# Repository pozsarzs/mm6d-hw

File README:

*** WARNING! It is not yet useable, because it is under development. WARNING ***

Short information
-----------------
MM6D * Remote controlled switching device
Copyright (C) 2020 Pozsár Zsolt <pozsar.zsolt@szerafingomba.hu>
Homepage: <http://www.szerafingomba.hu/equipments/>

Documentation
 - version:             1.0
 - licence:             CC-BY-NC-4.0
 - language:            en

Hardware
 - version:             v200612
 - architecture:        xtensa
 - operation system:    -

Software
 - version:             v0.1
 - licence:             EUPL v1.1
 - language:            en

*** WARNING! It is not yet useable, because it is under development. WARNING ***

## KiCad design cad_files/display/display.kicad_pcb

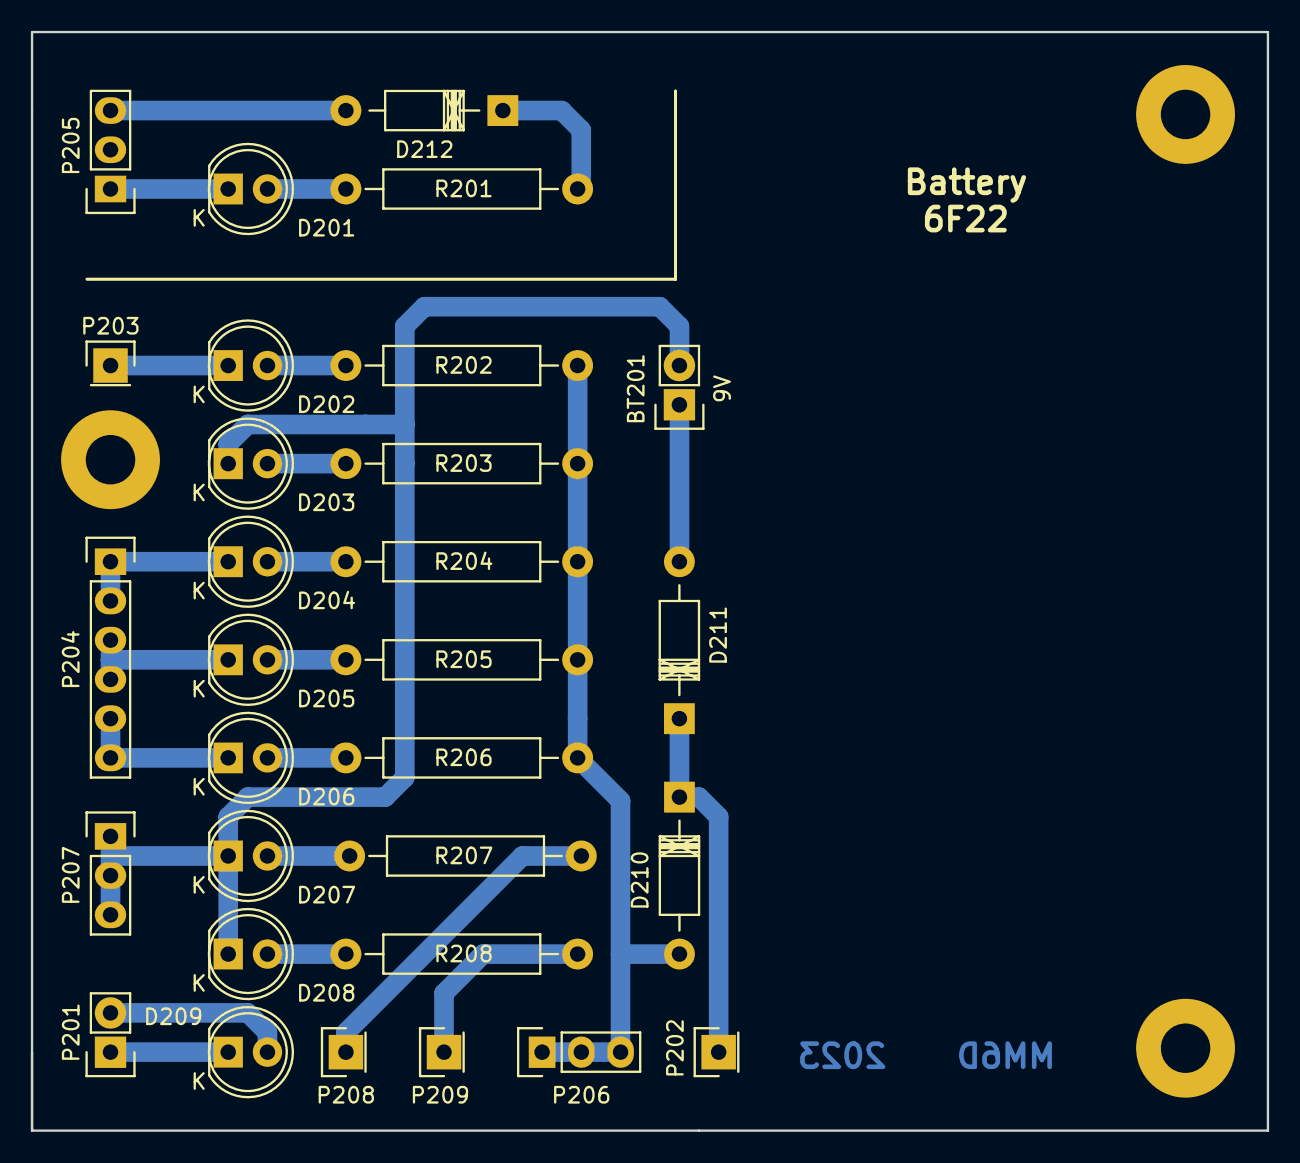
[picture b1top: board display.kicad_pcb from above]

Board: 2 copper layers, 80.0 x 71.1 mm, 30 parts (0 on the bottom side), 23 nets.

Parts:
BT201: 9V; Socket_Strip_Straight_1x02
D201, D203: white; LED-5MM
D202, D207: red; LED-5MM
D204, D205, D206: green; LED-5MM
D208: yellow; LED-5MM
D209: blue; LED-5MM
D210, D211: 1N4001; Diode_DO-41_SOD81_Horizontal_RM10
D212: 1N4007; Diode_DO-41_SOD81_Horizontal_RM10
P201: CONN_01X02; Socket_Strip_Straight_1x02
P202, P203, P208, P209: CONN_01X01; Socket_Strip_Straight_1x01
P204: CONN_01X06; Socket_Strip_Straight_1x06
P205, P206, P207: CONN_01X03; Socket_Strip_Straight_1x03
R201: 47k; Resistor_Horizontal_RM15mm
R202, R203: 1.5k; Resistor_Horizontal_RM15mm
R204, R205, R206, R207, R208: 1,5k; Resistor_Horizontal_RM15mm

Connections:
/+12V: D210.2, P206.1, P206.2, P206.3, R202.2, R203.2, R204.2, R205.2, R206.2
unnamed: BT201.1, D211.2
unnamed: BT201.2, D203.1, D207.1, D208.1, P207.1, P207.2, P207.3
unnamed: D201.1, P205.1
unnamed: D201.2, R201.1
unnamed: D202.1, P203.1
unnamed: D202.2, R202.1
unnamed: D203.2, R203.1
unnamed: D204.1, P204.1, P204.2
unnamed: D204.2, R204.1
unnamed: D205.1, P204.3, P204.4
unnamed: D205.2, R205.1
unnamed: D206.1, P204.5, P204.6
unnamed: D206.2, R206.1
unnamed: D207.2, R207.2
unnamed: D208.2, R208.1
unnamed: D209.1, P201.1
unnamed: D209.2, P201.2
unnamed: D210.1, D211.1, P202.1
unnamed: D212.1, R201.2
unnamed: D212.2, P205.3
unnamed: P208.1, R207.1
unnamed: P209.1, R208.2

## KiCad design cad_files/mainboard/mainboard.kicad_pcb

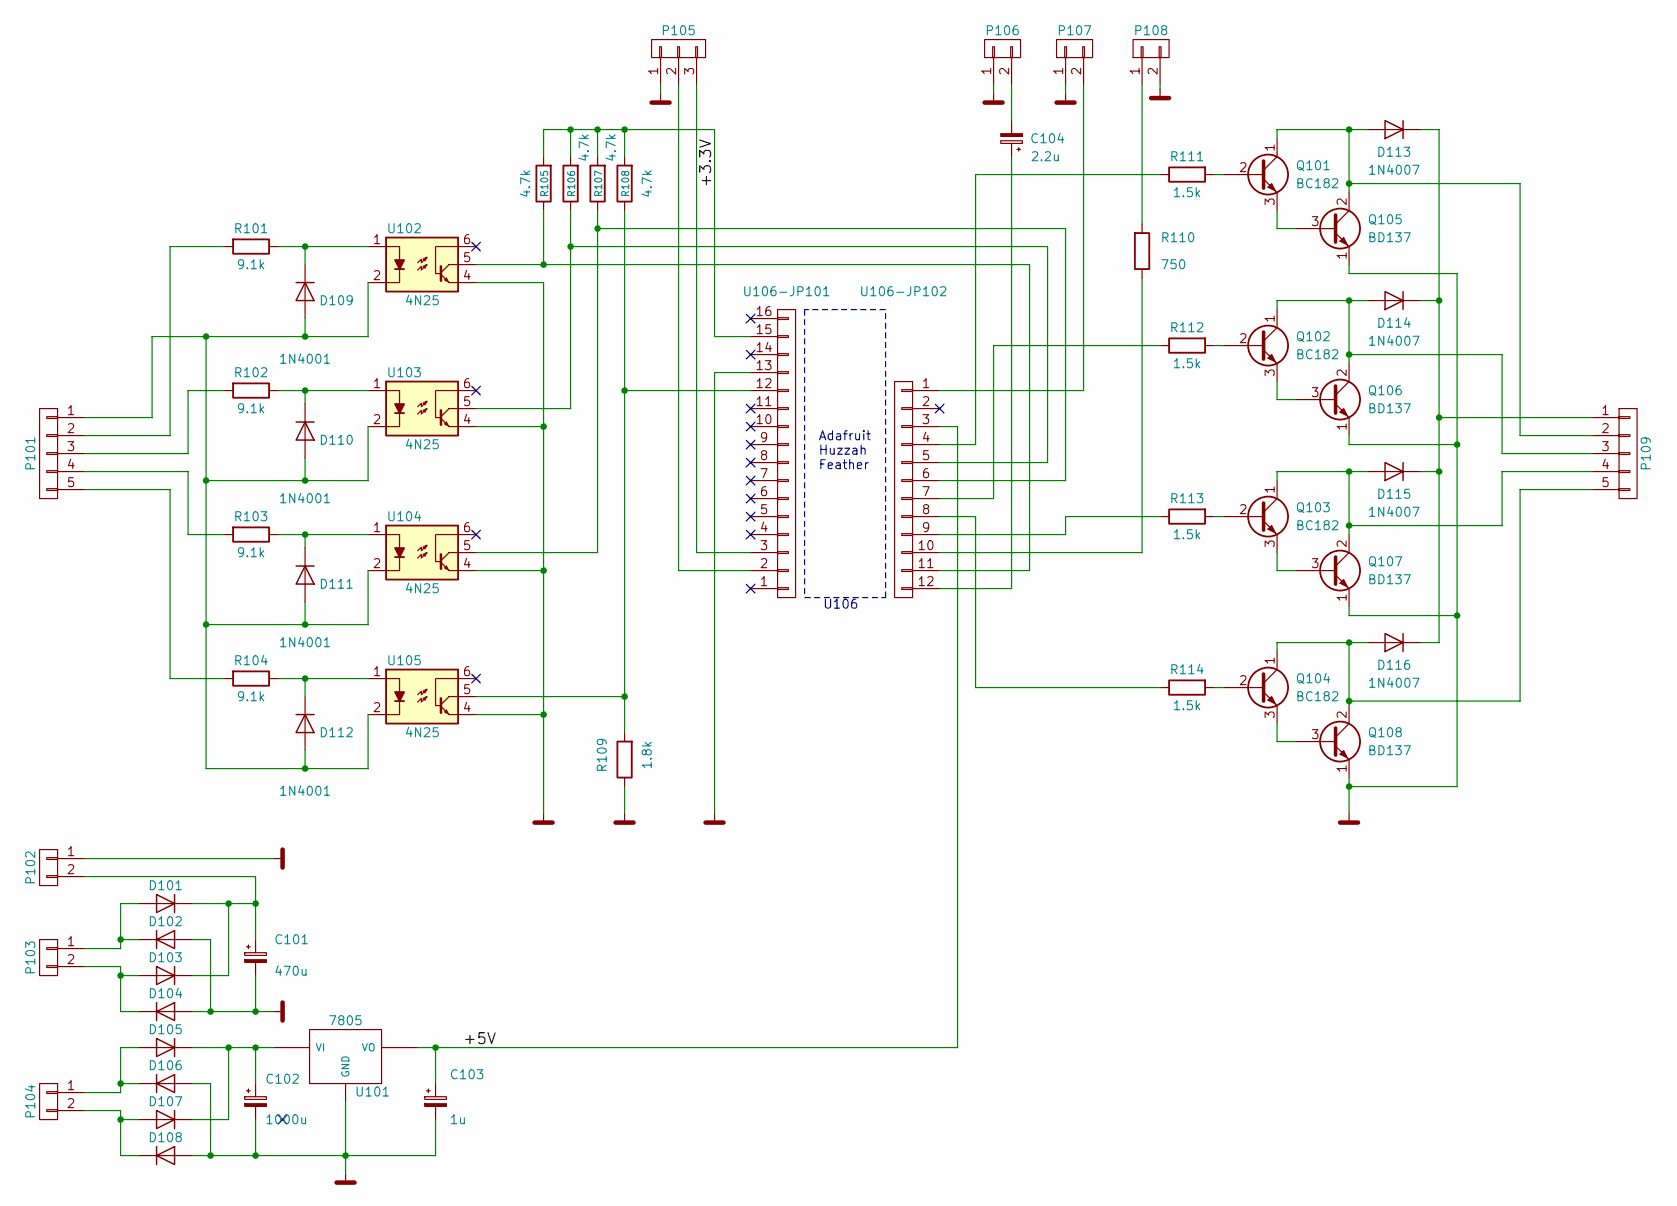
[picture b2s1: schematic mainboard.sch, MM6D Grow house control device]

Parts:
C101: 470u; C_Radial_D8_L11.5_P3.5
C102: 1000u; C_Radial_D8_L11.5_P3.5
C103: 1u; C_Rect_L7_W4.5_P5
C104: 2.2u; C_Rect_L7_W4.5_P5
D101, D102, D103, D104, D105, D106, D107, D108, D109, D110, D111, D112: 1N4001; Diode_DO-41_SOD81_Horizontal_RM10
D113, D114, D115, D116: 1N4007; Diode_DO-41_SOD81_Horizontal_RM10
P101, P109: CONN_01X05; Socket_Strip_Straight_1x05
P102, P103, P104, P106, P107, P108: CONN_01X02; Socket_Strip_Straight_1x02
P105: CONN_01X03; Socket_Strip_Straight_1x03
Q101, Q102, Q103, Q104: BC182; TO-92_Molded_Narrow
Q105, Q106, Q107, Q108: BD137; SOT126_SOT32_Housing_Horizontal
R101, R102, R103, R104: 9.1k; R3
R105, R106, R107, R108: 4.7k; R3
R109: 1.8k; R3
R110: 750; R3
R111, R112, R113, R114: 1.5k; R3
U101: 7805; TO-220_Neutral123_Horizontal_LargePads
U102, U103, U104, U105: 4N25; DIP-6_W7.62mm_LongPads
U106-JP101: CONN_01X16; Socket_Strip_Straight_1x16
U106-JP102: CONN_01X12; Socket_Strip_Straight_1x12

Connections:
/+3.3V: R105.2, R106.2, R107.2, R108.2, U106-JP101.15
/+5V: C103.1, U101.VO, U106-JP102.3
GND: C101.2, C102.2, C103.2, D102.2 (A), D104.2 (A), D106.2 (A), D108.2 (A), P102.1, P105.1, P106.1, P107.1, P108.2, Q105.1 (E), Q106.1 (E), Q107.1 (E), Q108.1 (E), R109.1, U101.GND, U102.4, U103.4, U104.4, U105.4, U106-JP101.13
unnamed: C101.1, D101.1 (K), D103.1 (K), P102.2
unnamed: C102.1, D105.1 (K), D107.1 (K), U101.VI
unnamed: C104.1, U106-JP102.12
unnamed: C104.2, P106.2
unnamed: D101.2 (A), D102.1 (K), P103.1
unnamed: D103.2 (A), D104.1 (K), P103.2
unnamed: D105.2 (A), D106.1 (K), P104.1
unnamed: D107.2 (A), D108.1 (K), P104.2
unnamed: D109.1 (K), R101.1, U102.1
unnamed: D109.2 (A), D110.2 (A), D111.2 (A), D112.2 (A), P101.1, U102.2, U103.2, U104.2, U105.2
unnamed: D110.1 (K), R102.1, U103.1
unnamed: D111.1 (K), R103.1, U104.1
unnamed: D112.1 (K), R104.1, U105.1
unnamed: D113.1 (K), D114.1 (K), D115.1 (K), D116.1 (K), P109.1
unnamed: D113.2 (A), P109.2, Q101.1 (C), Q105.2 (C)
unnamed: D114.2 (A), P109.3, Q102.1 (C), Q106.2 (C)
unnamed: D115.2 (A), P109.4, Q103.1 (C), Q107.2 (C)
unnamed: D116.2 (A), P109.5, Q104.1 (C), Q108.2 (C)
unnamed: P101.2, R101.2
unnamed: P101.3, R102.2
unnamed: P101.4, R103.2
unnamed: P101.5, R104.2
unnamed: P105.2, U106-JP101.2
unnamed: P105.3, U106-JP101.3
unnamed: P107.2, U106-JP102.1
unnamed: P108.1, R110.2
unnamed: Q101.2 (B), R111.2
unnamed: Q101.3 (E), Q105.3 (B)
unnamed: Q102.2 (B), R112.2
unnamed: Q102.3 (E), Q106.3 (B)
unnamed: Q103.2 (B), R113.2
unnamed: Q103.3 (E), Q107.3 (B)
unnamed: Q104.2 (B), R114.2
unnamed: Q104.3 (E), Q108.3 (B)
unnamed: R105.1, U102.5, U106-JP102.11
unnamed: R106.1, U103.5, U106-JP102.5
unnamed: R107.1, U104.5, U106-JP102.6
unnamed: R108.1, R109.2, U105.5, U106-JP101.12
unnamed: R110.1, U106-JP102.10
unnamed: R111.1, U106-JP102.4
unnamed: R112.1, U106-JP102.7
unnamed: R113.1, U106-JP102.9
unnamed: R114.1, U106-JP102.8

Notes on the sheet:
U106
Adafruit Huzzah Feather

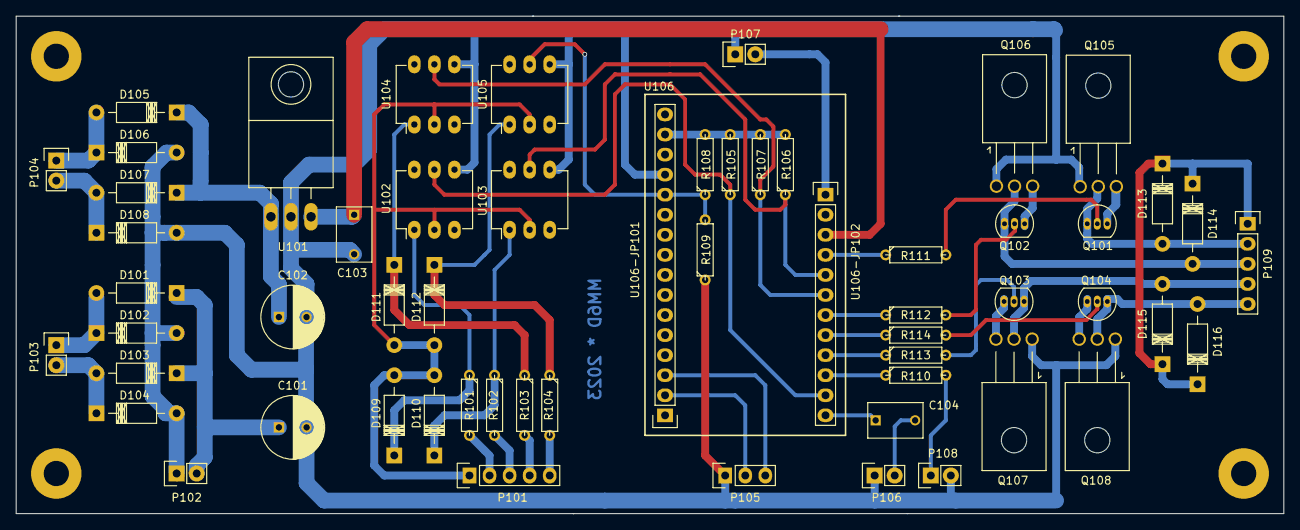
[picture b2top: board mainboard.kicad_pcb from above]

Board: 2 copper layers, 160.5 x 63.0 mm, 58 parts (0 on the bottom side), 46 nets.

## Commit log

2020-06-15 200615
2020-06-17 200617
2020-06-21 200621
2020-06-24 200624
2020-07-18 200718
2020-07-19 200719
2020-07-20 200720
2020-07-21 200721
2020-07-22 200722
2020-07-23 200723
2020-07-24 200724
2020-07-25 200725
2020-07-26 200726
2020-07-27 200727
2020-08-13 200813
2020-08-19 200819
2020-08-31 200831
2020-09-07 200907
2020-10-07 201007
2020-10-08 201008
2020-10-26 201026
2020-10-28 201028
2020-10-29 201029
2020-10-30 201030
2020-10-31 201031
2020-11-01 201101
2020-11-02 201102
2020-12-26 201226
2020-12-27 201227
2020-12-29 201229
2020-12-30 201230
2020-12-31 201231
2021-02-21 210221
2021-04-03 210403
2022-08-05 220805
2022-09-27 220927
2023-03-31 230331
2023-09-07 230907
2024-04-23 240423
2024-04-24 240424
